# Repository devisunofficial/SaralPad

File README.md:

# SaralPad

SaralPad is a 12 key macropad with two rotary encoder, an OLED Display. It uses QMK firmware

It focuses on minimalism and ease of getting work done with as minimum clicks as possible. For this it uses 3 profile layer in firmware for normal, browser and coding use.

### Features:

 - Compact design but strong because of middleplate.
 - 128x32 OLED Display
 - EC11 Rotary encoder for whatever you want.
 - 12 Keys

### CAD Model:
Everything fits together using 4 M3 Bolts and heatset inserts.

It has 3 separate printed pieces. The backplate, the Middle plate to support pcb, and Top to cover electronics.

Made in Autodesk Fusion.

### PCB:
Here's my PCB! It was made in KiCad. 

Schematic : 
PCB Footprint : 

### Firmware Overview:
Currently Firmware is underdevelopment so there is some time to finished product.
This Hackpad uses QMK Firmware for everything.
Features after completion:
 - Different key profile for different uses(Browsing, Coding, Gaming, and much more). 
 - One Rotatory encoder to change profile.
 - Oled Display to show key profile and different data about computer(Don't know if later is possible)

 I might add more in the future! That's it for now.

### BOM Table
|S. No.|Name|Use|Quantity|
|------|----|---|-----------|
|1|Cherry MX Switches|Switches|12|
|2|XIAO RP2040|Microcontroller|1|
|3|0.91" 128x32 OLED Display|Display|1|
|4|EC11 Rotary Encoder|Fidget Toy and Mode Selector|2|
|5|PCB|Main Circuit|1|
|6|KeyCaps |Keycaps for Cherry Switches|12|

 ### Extra Stuff:
 Learned few new things, realised I have short temper and I am quite dumb in some cases.
 Don't know what should I add more. 
 For future : I submitted this during war, I thought of not completing it as (not going to state as it is obvious), just tell   me my future-self :- Would you have regretted if hadn't submitted?

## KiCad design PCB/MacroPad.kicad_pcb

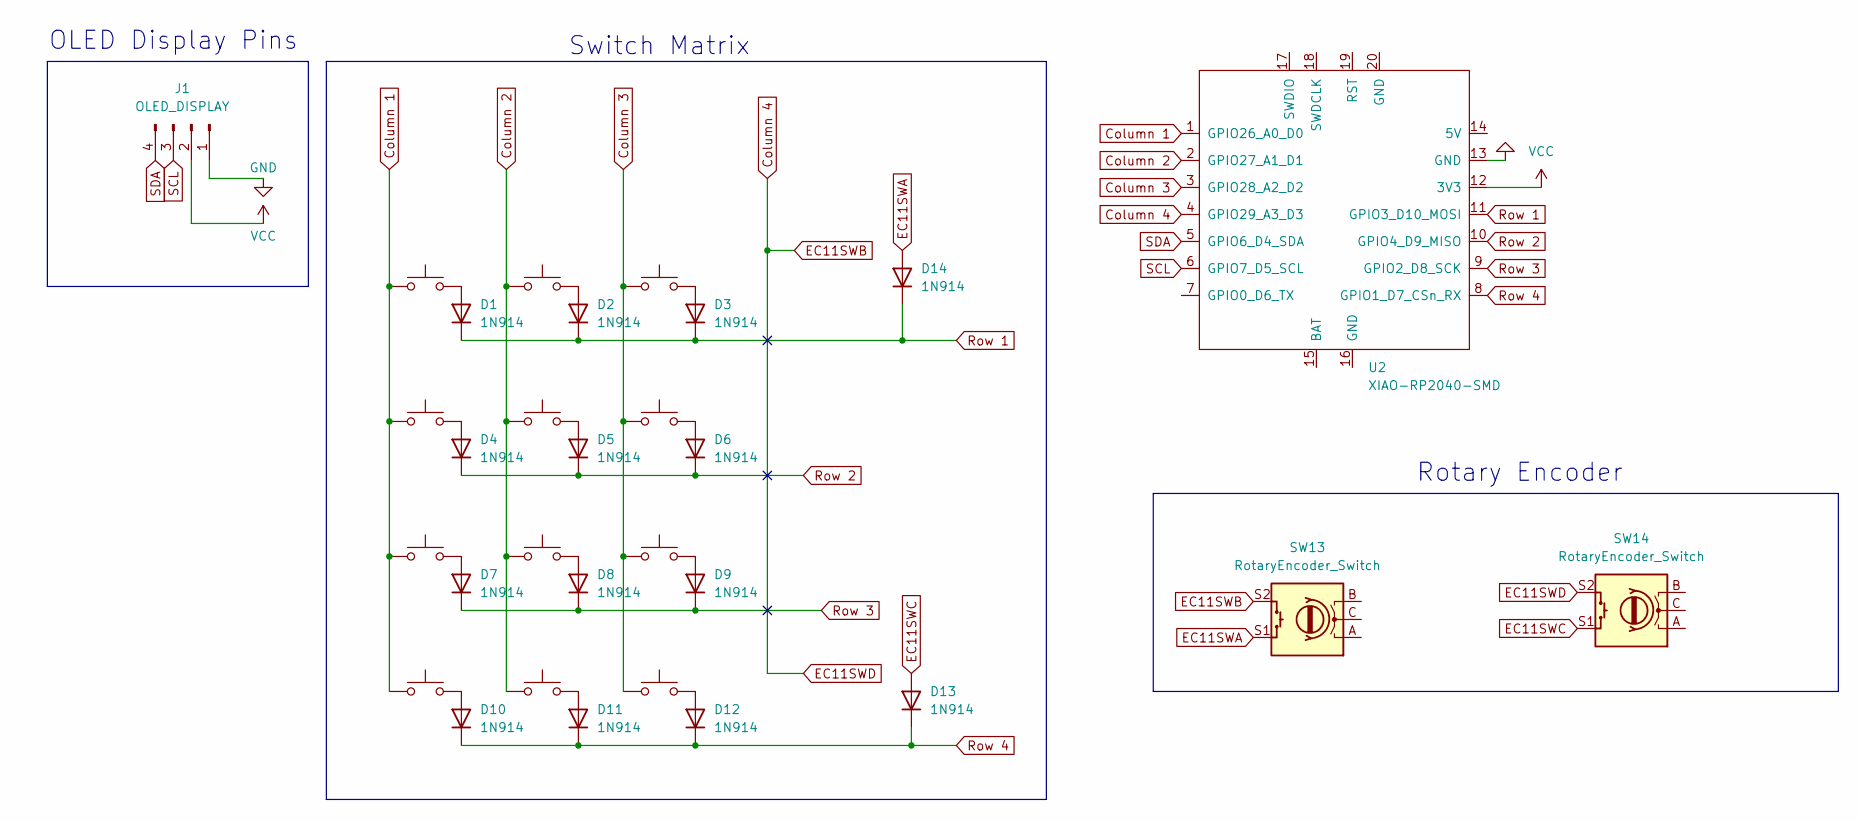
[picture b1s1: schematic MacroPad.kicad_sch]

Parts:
D1, D2, D3, D4, D5, D6, D7, D8, D9, D10, D11, D12, D13, D14: 1N914; D_DO-35_SOD27_P7.62mm_Horizontal
J1: OLED_DISPLAY; SSD1306-0.91-OLED-4pin-128x32
SW1, SW2, SW3, SW4, SW5, SW6, SW7, SW8, SW9, SW10, SW11, SW15: SW_Push; SW_Cherry_MX_1.00u_PCB
SW13, SW14: RotaryEncoder_Switch; RotaryEncoder_Alps_EC11E-Switch_Vertical_H20mm
U2: XIAO-RP2040-SMD; XIAO-Generic-Hybrid-14P-2.54-21X17.8MM

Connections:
Column 1: SW3.1, SW6.1, SW7.1, SW15.1, U2.1 (GPIO26_A0_D0)
Column 2: SW1.1, SW4.1, SW8.1, SW10.1, U2.2 (GPIO27_A1_D1)
Column 3: SW2.1, SW5.1, SW9.1, SW11.1, U2.3 (GPIO28_A2_D2)
Column 4: SW13.S2, SW14.S2, U2.4 (GPIO29_A3_D3)
EC11SWA: D14.2 (A), SW13.S1
EC11SWC: D13.2 (A), SW14.S1
GND: J1.1, U2.13 (GND)
unnamed: D1.2 (A), SW15.2
unnamed: D2.2 (A), SW1.2
unnamed: D3.2 (A), SW2.2
unnamed: D4.2 (A), SW3.2
unnamed: D5.2 (A), SW4.2
unnamed: D6.2 (A), SW5.2
unnamed: D7.2 (A), SW7.2
unnamed: D8.2 (A), SW8.2
unnamed: D9.2 (A), SW9.2
unnamed: D10.2 (A), SW6.2
unnamed: D11.2 (A), SW10.2
unnamed: D12.2 (A), SW11.2
Row 1: D1.1 (K), D2.1 (K), D3.1 (K), D14.1 (K), U2.11 (GPIO3_D10_MOSI)
Row 2: D4.1 (K), D5.1 (K), D6.1 (K), U2.10 (GPIO4_D9_MISO)
Row 3: D7.1 (K), D8.1 (K), D9.1 (K), U2.9 (GPIO2_D8_SCK)
Row 4: D10.1 (K), D11.1 (K), D12.1 (K), D13.1 (K), U2.8 (GPIO1_D7_CSn_RX)
SCL: J1.3, U2.6 (GPIO7_D5_SCL)
SDA: J1.4, U2.5 (GPIO6_D4_SDA)
VCC: J1.2, U2.12 (3V3)

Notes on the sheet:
Rotary Encoder
OLED Display Pins
Switch Matrix

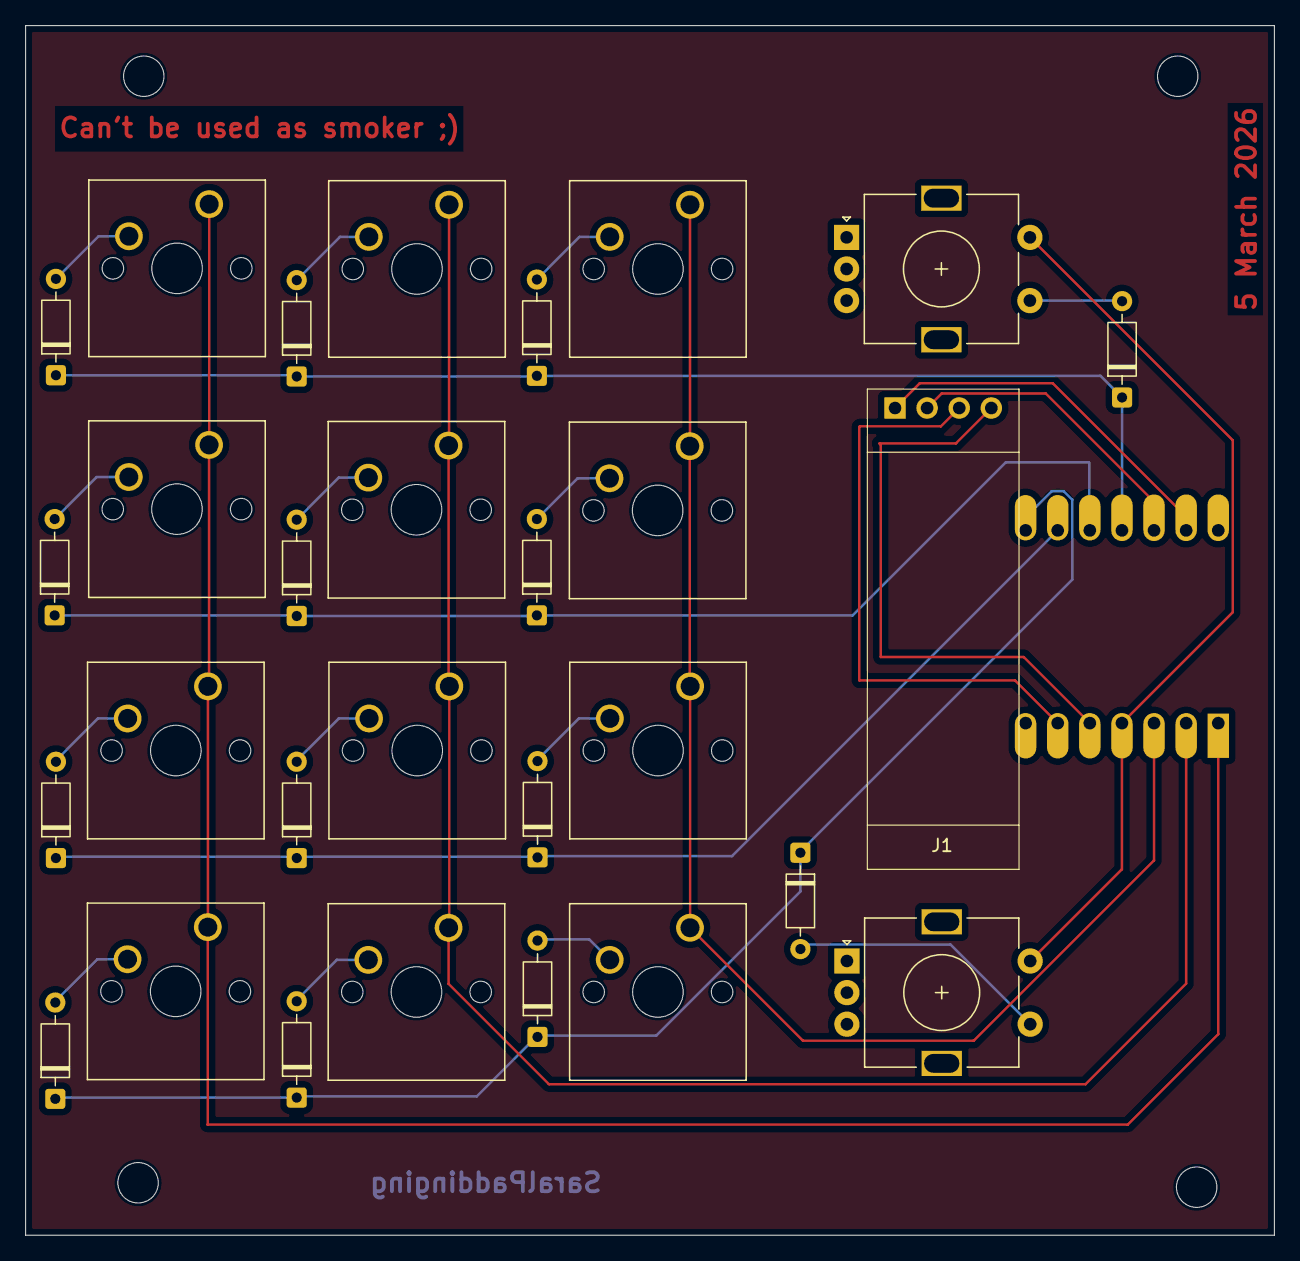
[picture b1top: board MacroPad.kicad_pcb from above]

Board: 2 copper layers, 98.8 x 95.7 mm, 30 parts (1 on the bottom side), 26 nets.

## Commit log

2026-03-29 Final
2026-03-29 Done
2026-03-31 Final 2
2026-04-02 Done !!
2026-04-12 partial
2026-04-12 Last Chance
2026-06-07 FINALL
2026-06-12 Bom added
2026-06-12 Add component list with details to README
    Added a table listing components with details including name, purpose, quantity, total cost, links, and distributors.
2026-06-12 Readme Done
2026-06-12 Possibly Final
2026-06-12 Update bom.csv with additional keycap entry
2026-06-12 Finallyy
2026-06-14 Final I guess
